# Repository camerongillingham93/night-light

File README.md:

# Firefly Night-Light
#### February, 13, 2025
 - Development REPO for a nightlight project using the AT-TINY1614 MCU and addressable LED strips
## Features 
 - PCB is designed to replace a standard wide-mouth Mason jar and have LED strips hanging from it resembling a jar full of fireflies
 - Top copper pad acts as a touch button to toggle the nightlight on/off and adjust brightness. Shake the jar for a firefly lightshow
 - Onboard LI-PO battery that is USB-C re-chargeable

<br>
*Rendering of Top of the night-light PCB*

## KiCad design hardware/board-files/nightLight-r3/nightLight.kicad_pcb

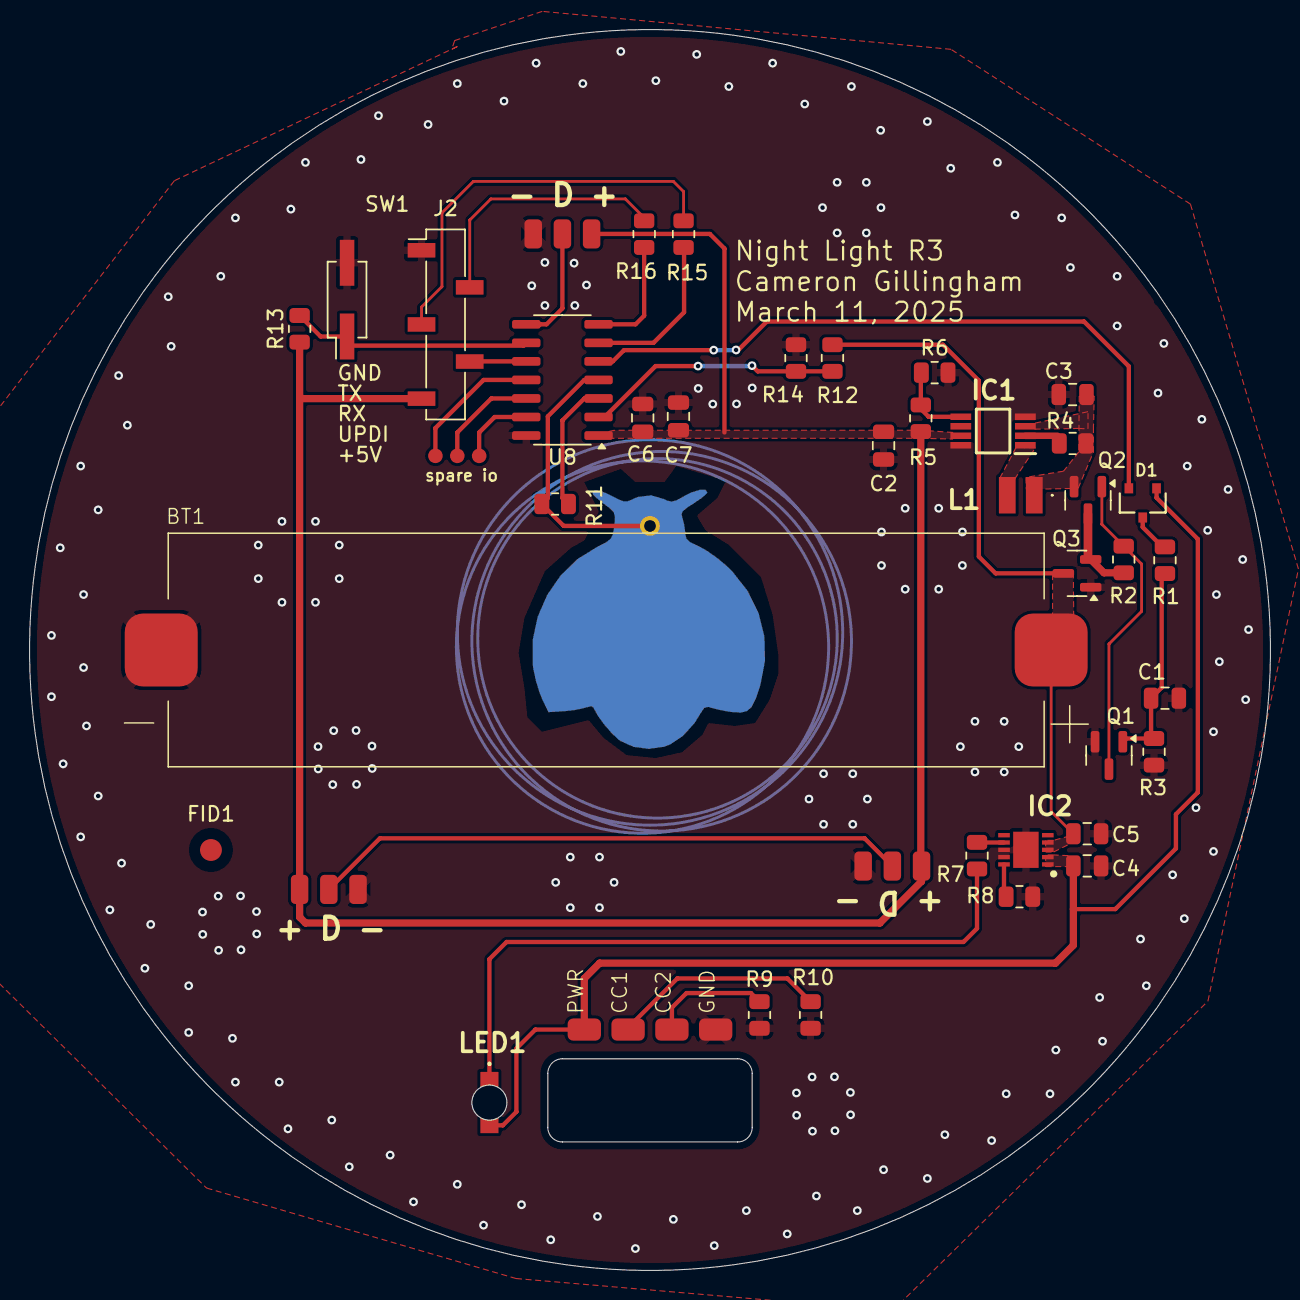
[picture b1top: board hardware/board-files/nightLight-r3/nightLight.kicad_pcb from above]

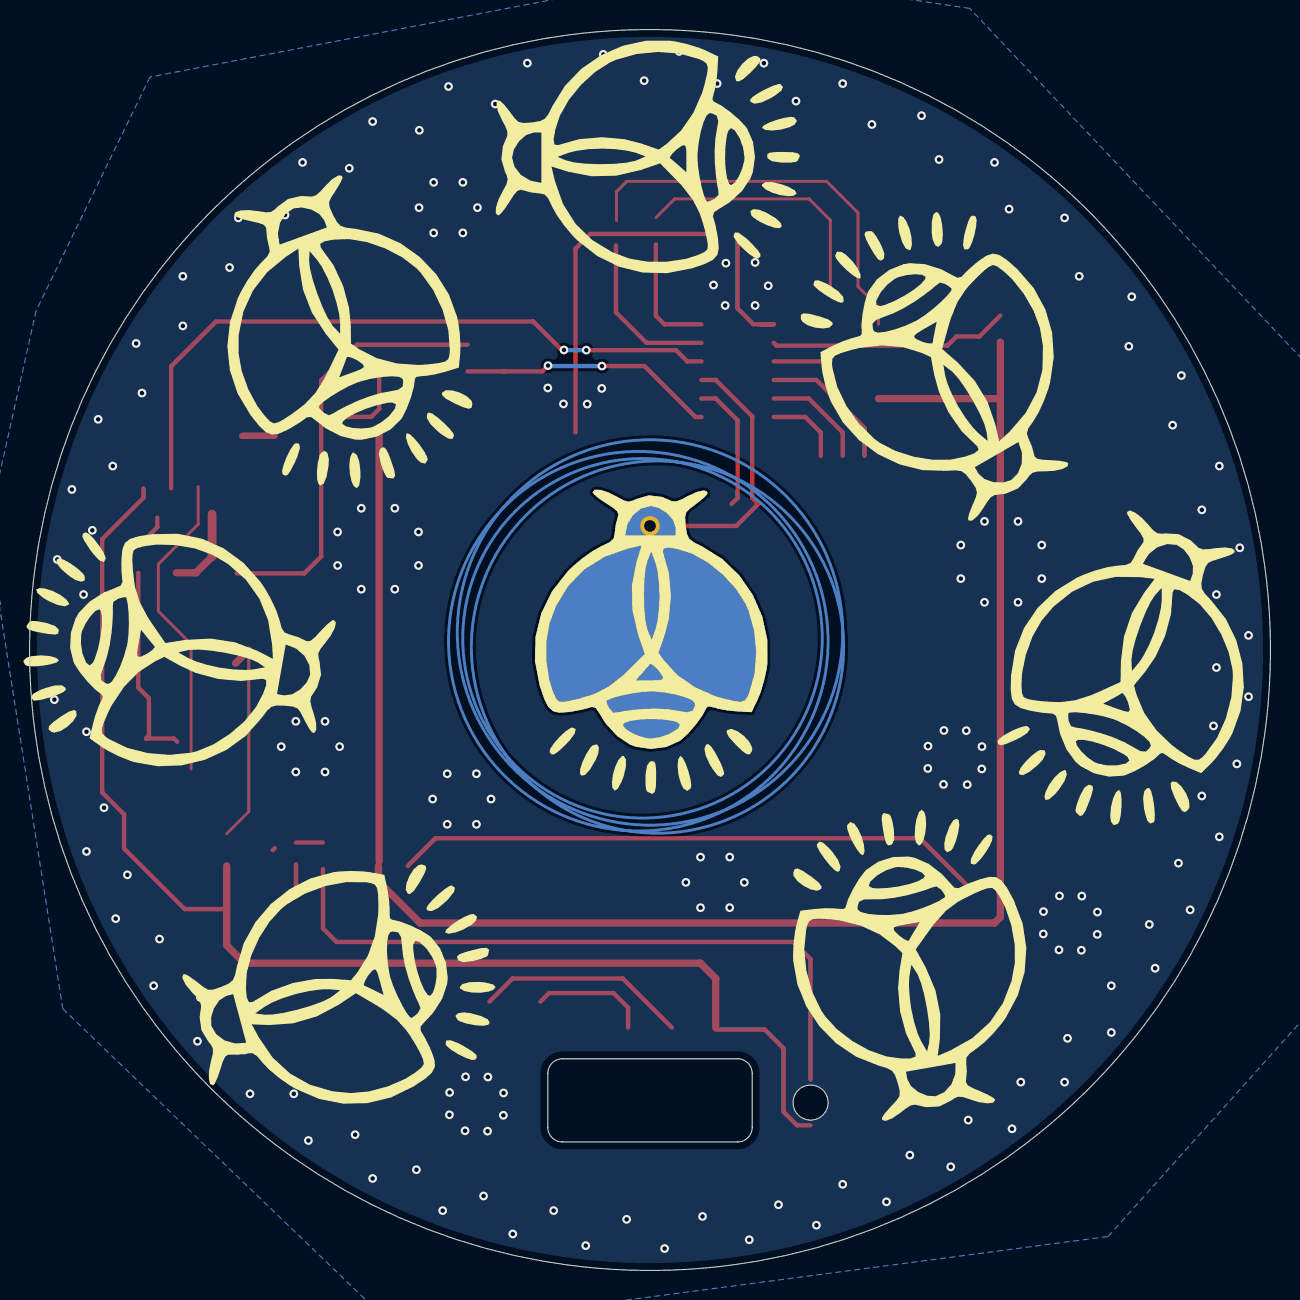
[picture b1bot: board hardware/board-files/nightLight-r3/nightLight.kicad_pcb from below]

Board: 2 copper layers, 85.0 x 85.0 mm, 49 parts (8 on the bottom side), 32 nets.

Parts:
B1: fireflyTouch
BT1: Battery_Cell; 14500 Holder
C1, C7: 0.1uF; C_0805_2012Metric
C2, C3, C6: 22uF; C_0805_2012Metric
C4, C5: 4.7uF; C_0805_2012Metric
D1: BAT54C; SOT23-R
FID1: Fiducial; Fiducial_1.5mm_Mask3mm
IC1: PAM2401SCADJ; SOP65P490X110-8N
IC2: MCP73123T-22SI_MF; SON50P300X300X100-11N-D
J1: USB_C_Receptacle_PowerOnly_6P; USB-C_PWR
J2: Conn_01x05_Pin; PinSocket_1x05_P2.54mm_Vertical_SMD_Pin1Left
J3: Conn_01x03; spares_1*3
J4, J5, J6: Conn_01x03; fairy_conn
L1: SRN2510BTA-2R2M; SRN2510BTA2R2M
LED1: IN-S124ARUW; INS124ARUW
Q1: AO3400A; SOT-23
Q2, Q3: AO3401A; SOT-23
R1: 10K; R_0805_2012Metric
R2, R3, R11, R12, R14: 1M; R_0805_2012Metric
R4, R5: 750K; R_0805_2012Metric
R6: 100K; R_0805_2012Metric
R7: 1K; R_0805_2012Metric
R8: 5.1K; R_0805_2012Metric
R9, R10: 5.1k; R_0805_2012Metric
R13: 10k; R_0805_2012Metric
R15, R16: 0; R_0805_2012Metric
SW1: TILT; PinHeader_2x01_P2.54mm_Vertical_SMD
U1, U2, U3, U4, U5, U6, U7: fireflyTouchNB
U8: ATtiny1614-SS; SOIC-14_3.9x8.7mm_P1.27mm

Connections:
+5V: C2.1, C6.1, C7.1, IC1.7 (OUT), J2.5, J4.1, J5.1, J6.1, R5.2, R13.1, U8.1 (VCC)
/Charge Controller/Vbatt: BT1.1 (+), C5.1, IC2.3 (VBAT_1), IC2.4 (VBAT_2), Q3.3 (D), R12.1
/Charge Controller/Vbus: C4.1, D1.1, IC2.1 (VDD_1), IC2.2 (VDD_2), J1.A9 (VBUS), LED1.2 (A)
/MCU/BATT_M: R12.2, R14.1, U8.2 (PA4)
/MCU/FET_CONTROL: D1.2, U8.5 (PA7)
/MCU/LED_DATA: J4.2, U8.8 (PB1)
/MCU/PA_1: J3.1, U8.11 (PA1)
/MCU/PA_2: J3.2, U8.12 (PA2)
/MCU/PA_3: J3.3, U8.13 (PA3)
/MCU/RETURN: B1.1, R11.2, U8.4 (PA6)
/MCU/RX: R15.1, U8.6 (PB3)
/MCU/SEND: R11.1, U8.3 (PA5)
/MCU/TILT_SW: R13.2, SW1.1, U8.9 (PB0)
/MCU/TX: R16.1, U8.7 (PB2)
/MCU/UPDI: J2.4, U8.10 (~RESET/PA0)
GND: BT1.2 (-), C1.2, C2.2, C3.2, C4.2, C5.2, C6.2, C7.2, IC1.4 (AGND), IC1.8 (PGND), IC2.8 (VSS_1), IC2.9 (VSS_2), IC2.11 (EP), J1.A12 (GND), J2.1, J4.3, J5.3, J6.3, Q1.2 (S), Q3.1 (G), R3.2, R6.1, R8.2, R9.2, R10.2, R14.2, SW1.2, U8.14 (GND)
unnamed: D1.3, R1.2
unnamed: IC1.2 (EN), R4.2
unnamed: IC1.5 (FB), R5.1, R6.2
unnamed: IC1.1 (LX), L1.2
unnamed: C3.1, IC1.3 (VIN), L1.1, Q2.2 (S), R4.1
unnamed: IC2.10 (PROG), R8.1
unnamed: IC2.7 (STAT), R7.2
unnamed: J1.A5 (CC1), R10.1
unnamed: J1.B5 (CC2), R9.1
unnamed: J2.2, R16.2
unnamed: J2.3, R15.2
unnamed: J5.2, J6.2
unnamed: LED1.1 (K), R7.1
unnamed: Q1.3 (D), Q2.1 (G), R2.2
unnamed: C1.1, Q1.1 (G), R1.1, R3.1
unnamed: Q2.3 (D), Q3.2 (S), R2.1

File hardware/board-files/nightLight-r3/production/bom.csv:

Designator,Footprint,Quantity,Value,LCSC Part #
B1,fireflyTouch,1,~,
BT1,14500 Holder,1,Battery_Cell,
"C1, C7",0805,2,0.1uF,
"C2, C3, C6",0805,3,22uF,
"C4, C5",0805,2,4.7uF,
D1,SOT23-R,1,BAT54C,
FID1,Fiducial_1.5mm_Mask3mm,1,Fiducial,
IC1,SOP65P490X110-8N,1,PAM2401SCADJ,
IC2,SON50P300X300X100-11N-D,1,MCP73123T-22SI_MF,
J1,USB-C_PWR,1,USB_C_Receptacle_PowerOnly_6P,
J2,PinSocket_1x05_P2.54mm_Vertical_SMD_Pin1Left,1,Conn_01x05_Pin,
J3,spares_1*3,1,Conn_01x03,
"J4, J5, J6",fairy_conn,3,Conn_01x03,
L1,SRN2510BTA2R2M,1,SRN2510BTA-2R2M,
LED1,INS124ARUW,1,IN-S124ARUW,
Q1,SOT-23,1,AO3400A,
"Q2, Q3",SOT-23,2,AO3401A,
"R1, R13",0805,2,10K,
"R10, R8, R9",0805,3,5.1k,
"R11, R12, R14, R2, R3",0805,5,1M,
"R15, R16",0805,2,0,
"R4, R5",0805,2,750K,
R6,0805,1,100K,
R7,0805,1,1K,
SW1,PinHeader_2x01_P2.54mm_Vertical_SMD,1,TILT,
U8,SOIC-14_3.9x8.7mm_P1.27mm,1,ATtiny1614-SS,

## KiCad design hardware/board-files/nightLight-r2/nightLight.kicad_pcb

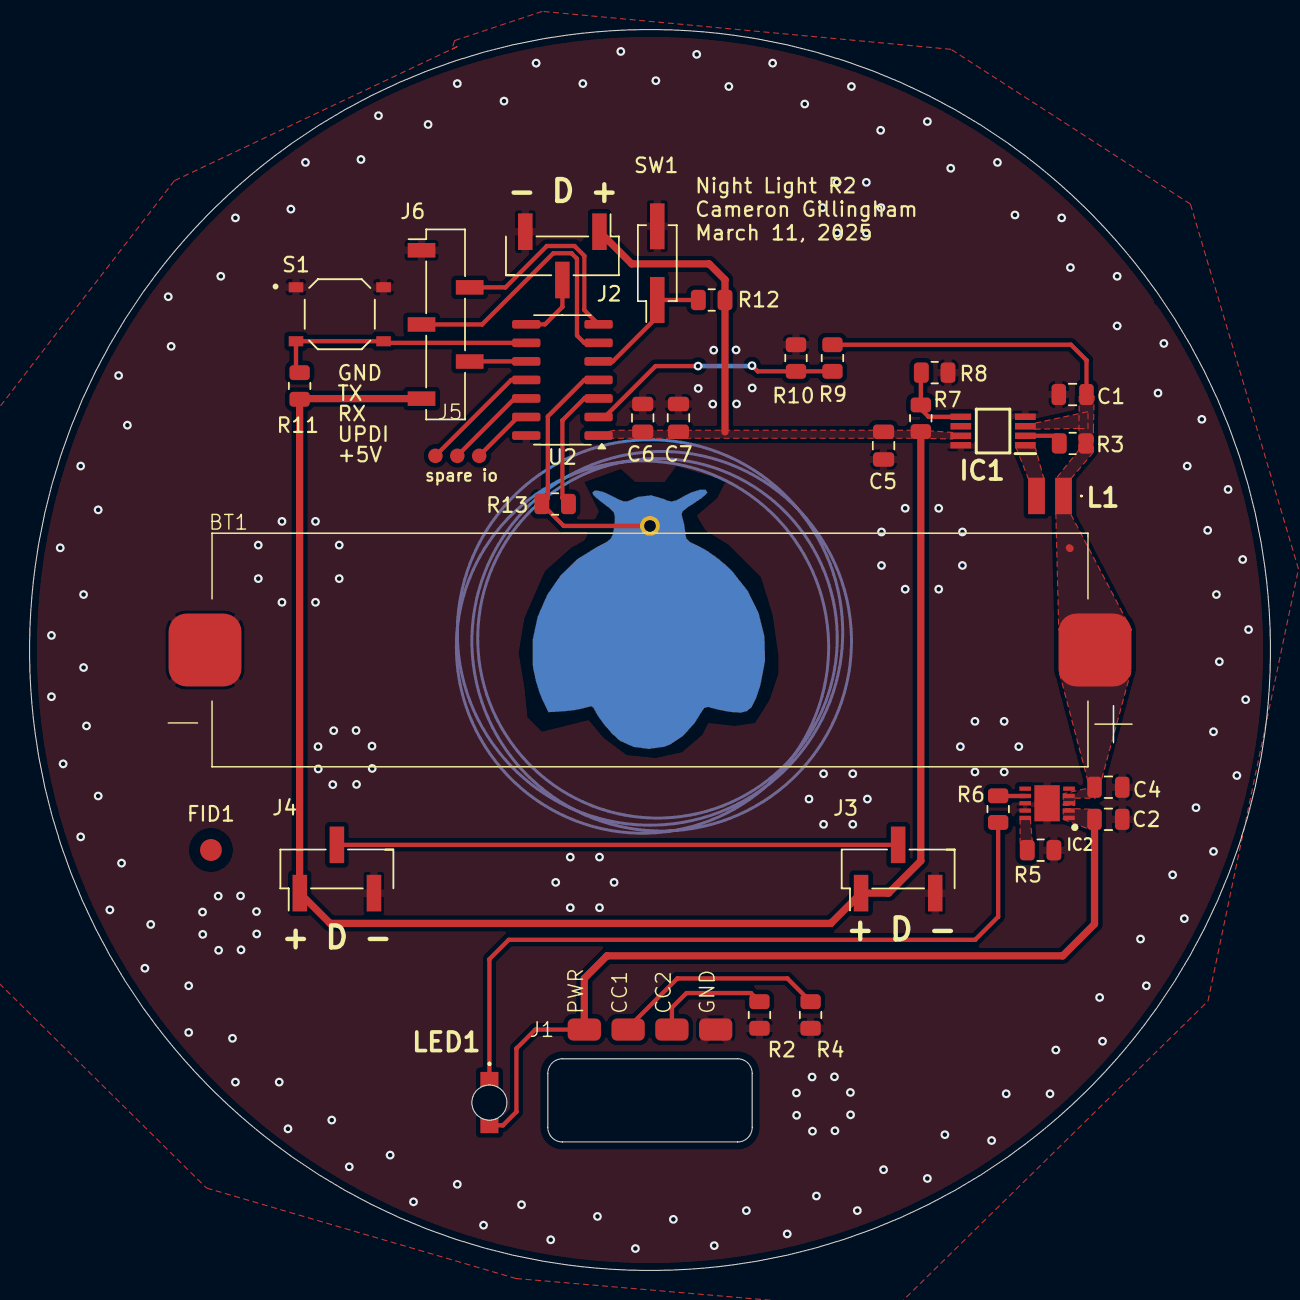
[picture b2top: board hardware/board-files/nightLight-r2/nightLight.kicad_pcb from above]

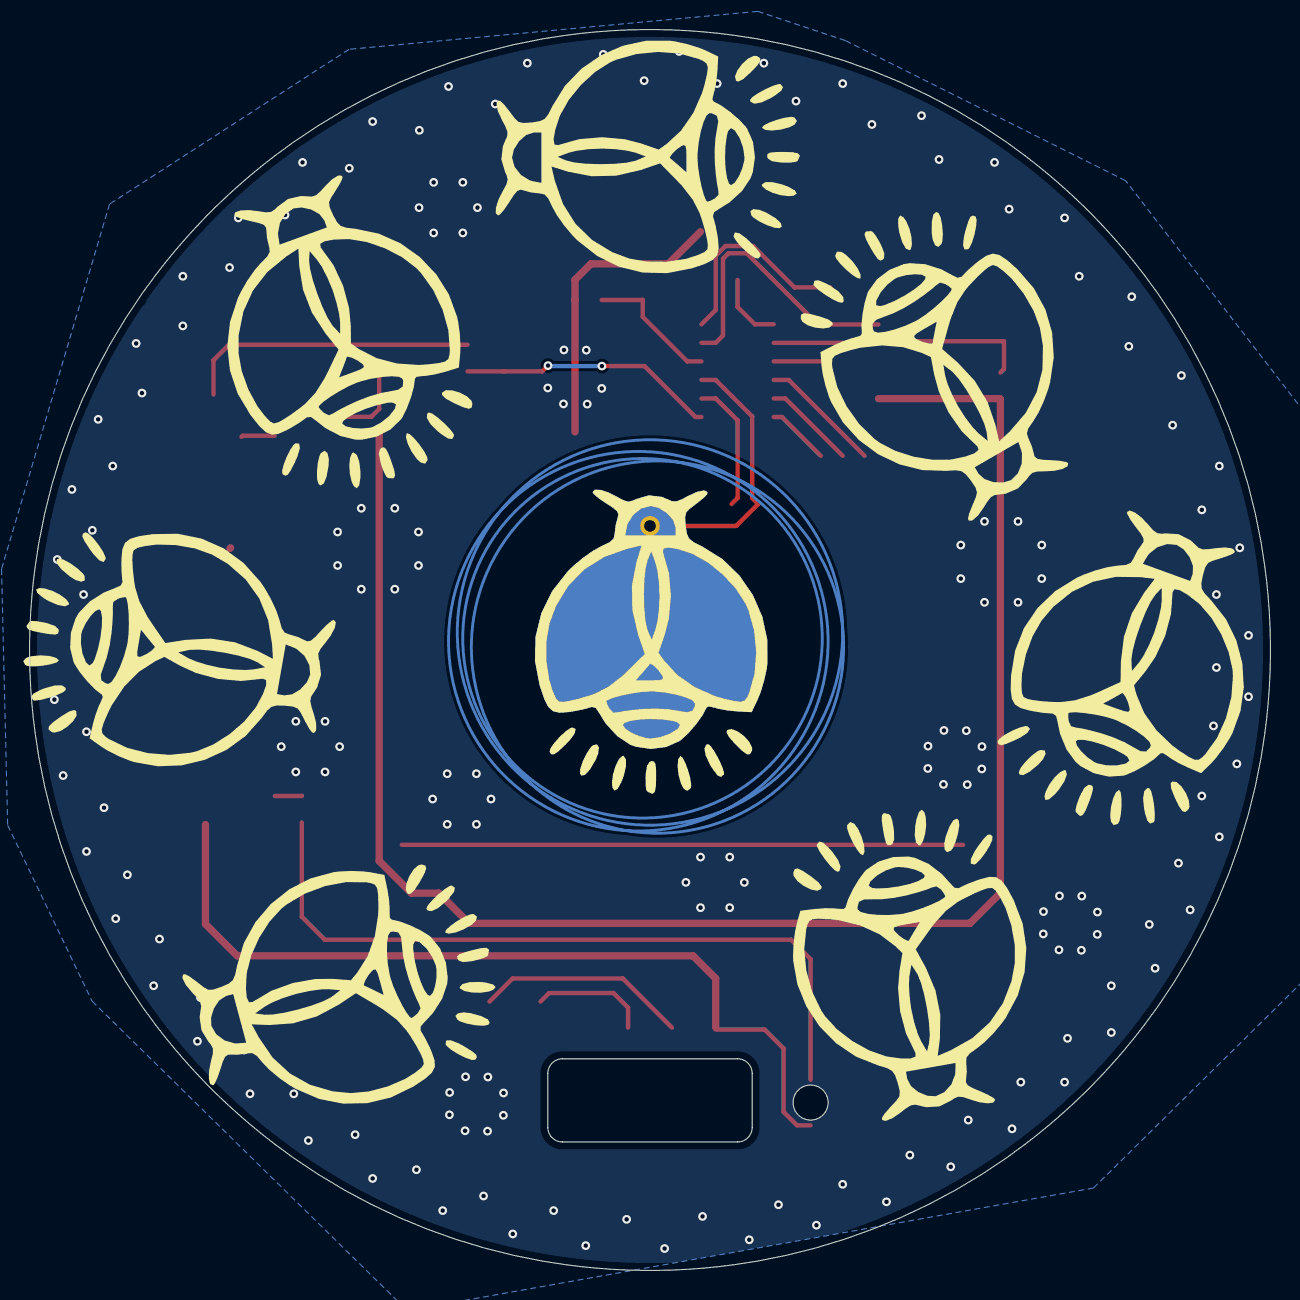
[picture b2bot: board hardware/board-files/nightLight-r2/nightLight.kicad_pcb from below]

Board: 2 copper layers, 85.0 x 85.0 mm, 41 parts (8 on the bottom side), 25 nets.

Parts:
B1: fireflyTouch
BT1: Battery_Cell; 14500 Holder
C1, C5, C6: 22uF; C_0805_2012Metric
C2, C4: 4.7uF; C_0805_2012Metric
C7: 0.1uF; C_0805_2012Metric
FID1: Fiducial; Fiducial_1.5mm_Mask3mm
IC1: PAM2401SCADJ; SOP65P490X110-8N
IC2: MCP73123T-22SI_MF; SON50P300X300X100-11N-D
J1: USB_C_Receptacle_PowerOnly_6P; USB-C_PWR
J2, J3, J4: Conn_01x03; PinHeader_1x03_P2.54mm_Vertical_SMD_Pin1Left
J5: Conn_01x03; spares_1*3
J6: Conn_01x05_Pin; PinSocket_1x05_P2.54mm_Vertical_SMD_Pin1Left
L1: SRN2510BTA-2R2M; SRN2510BTA2R2M
LED1: IN-S124ARUW; INS124ARUW
R2, R4: 5.1k; R_0805_2012Metric
R3, R7: 750K; R_0805_2012Metric
R5: 5.1K; R_0805_2012Metric
R6: 1K; R_0805_2012Metric
R8: 100K; R_0805_2012Metric
R9, R10: 0; R_0805_2012Metric
R11, R12: 10k; R_0805_2012Metric
R13: 1M; R_0805_2012Metric
S1: PTS526_SM08_SMTR2_LFS; SW_PTS526_SM08_SMTR2_LFS
SW1: TILT; PinHeader_2x01_P2.54mm_Vertical_SMD
U2: ATtiny1614-SS; SOIC-14_3.9x8.7mm_P1.27mm
U3, U4, U5, U6, U7, U8, U9: fireflyTouchNB

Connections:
+5V: C5.1, C6.1, C7.1, IC1.7 (OUT), J2.1, J3.1, J4.1, J6.5, R7.2, R11.1, R12.1, U2.1 (VCC)
Batt_M: R9.2, R10.1, U2.2 (PA4)
GND: BT1.2 (-), C1.2, C2.2, C4.2, C5.2, C6.2, C7.2, IC1.4 (AGND), IC1.8 (PGND), IC2.8 (VSS_1), IC2.9 (VSS_2), IC2.11 (EP), J1.A12 (GND), J2.3, J3.3, J4.3, J6.1, R2.2, R4.2, R5.2, R8.1, R10.2, S1.1, S1.2, SW1.2, U2.14 (GND)
LED_DATA: J2.2, U2.8 (PB1)
unnamed: IC1.2 (EN), R3.2
unnamed: IC1.5 (FB), R7.1, R8.2
unnamed: IC1.1 (LX), L1.2
unnamed: IC2.10 (PROG), R5.1
unnamed: IC2.7 (STAT), R6.2
unnamed: C2.1, IC2.1 (VDD_1), IC2.2 (VDD_2), J1.A9 (VBUS), LED1.2 (A)
unnamed: J1.A5 (CC1), R4.1
unnamed: J1.B5 (CC2), R2.1
unnamed: J3.2, J4.2
unnamed: LED1.1 (K), R6.1
PA_1: J5.1, U2.11 (PA1)
PA_2: J5.2, U2.12 (PA2)
PA_3: J5.3, U2.13 (PA3)
RST_SW: R11.2, S1.3, S1.4, U2.9 (PB0)
RX: J6.3, U2.6 (PB3)
Return: B1.1, R13.2, U2.4 (PA6)
Send: R13.1, U2.3 (PA5)
TX: J6.2, U2.7 (PB2)
Tilt_SW: R12.2, SW1.1, U2.5 (PA7)
UPDI: J6.4, U2.10 (~RESET/PA0)
VBATT: BT1.1 (+), C1.1, C4.1, IC1.3 (VIN), IC2.3 (VBAT_1), IC2.4 (VBAT_2), L1.1, R3.1, R9.1

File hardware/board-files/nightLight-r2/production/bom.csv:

Designator,Footprint,Quantity,Value,LCSC Part #,,Mouser Cart,Already Have,JLC,Wal-Mart Batteries,,
B1,fireflyTouch,1,~,,,N/A,X,,https://www.walmart.ca/en/ip/12-Pack-AA-3-2-Volt-600-mAh-LiF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,,
BT1,14500 Holder,1,Battery_Cell,,,N/A,X,,,,
"C1, C5, C6",0805,3,22uF,,,X,,,,,
"C2, C4",0805,2,4.7uF,,,X,,,,,
C7,0805,1,0.1uF,,,X,,,,,
FID1,Fiducial_1.5mm_Mask3mm,1,Fiducial,,,,X,,,,
IC1,SOP65P490X110-8N,1,PAM2401SCADJ,,,X,,,,,
IC2,SON50P300X300X100-11N-D,1,MCP73123T-22SI_MF,,,X,,,,,
J1,USB-C_PWR,1,USB_C_Receptacle_PowerOnly_6P,,,,X,,,,
"J2, J3, J4",PinHeader_1x03_P2.54mm_Vertical_SMD_Pin1Left,3,Conn_01x03,,,,X,,,,
J5,spares_1*3,1,Conn_01x03,,,,X,,,,
J6,PinSocket_1x05_P2.54mm_Vertical_SMD_Pin1Left,1,Conn_01x05_Pin,,,,X,,,,
L1,SRN2510BTA2R2M,1,SRN2510BTA-2R2M,,,X,,,,,
LED1,INS124ARUW,1,IN-S124ARUW,,,X,,,,,
"R10, R9",0805,2,0,,,X,,,,,
"R11, R12",0805,2,10k,,,X,,,,,
R13,0805,1,1M,,,X,,,,,
"R2, R4, R5",0805,3,5.1k,,,X,,,,,
"R3, R8",0805,2,100K,,,X,,,,,
R6,0805,1,1K,,,X,,,,,
R7,0805,1,750K,,,X,,,,,
S1,SW_PTS526_SM08_SMTR2_LFS,1,PTS526_SM08_SMTR2_LFS,,,X,,,,,
SW1,PinHeader_2x01_P2.54mm_Vertical_SMD,1,TILT,,,,X,,,,
U1,SOT95P237X112-3N,1,MCP809T-270I_TT,,,X,,,,,
U2,SOIC-14_3.9x8.7mm_P1.27mm,1,ATtiny1614-SS,,,X,,,,,
,,,,,,,,,,,
Total,,,,,,80,0,19.16,85.77,,184.93
/unit,,,,,,8,,3.83,7,,18.83

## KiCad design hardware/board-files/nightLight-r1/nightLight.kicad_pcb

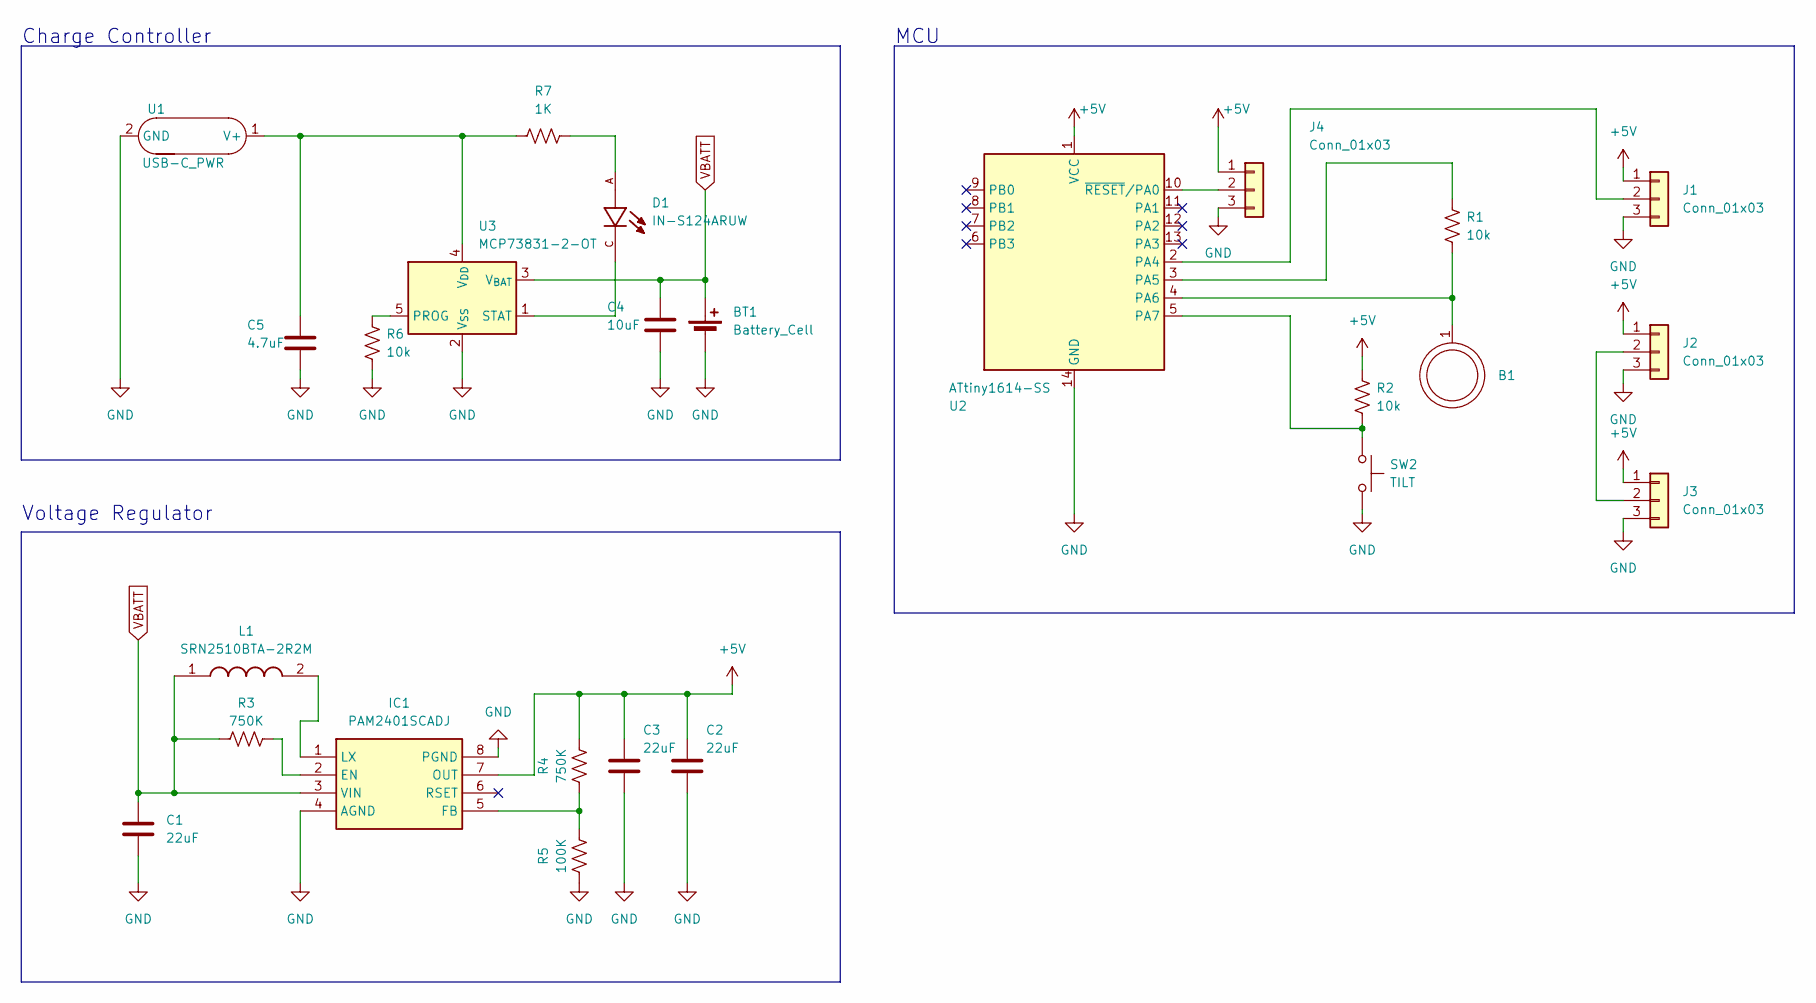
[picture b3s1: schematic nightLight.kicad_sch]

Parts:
B1: fireflyTouch
BT1: Battery_Cell; 14500 Holder
C1, C2, C3: 22uF; C_1206_3216Metric
C4: 10uF; C_1206_3216Metric
C5: 4.7uF; C_1206_3216Metric
D1: IN-S124ARUW; LED_IN-S124ARUW
IC1: PAM2401SCADJ; SOP65P490X110-8N; Mouser Part Number 621-PAM2401SCADJ
J1, J2, J3, J4: Conn_01x03; PinHeader_1x03_P2.54mm_Vertical_SMD_Pin1Left
L1: SRN2510BTA-2R2M; SRN2510BTA2R2M; Mouser Part Number 652-SRN2510BTA-2R2M
R1, R2, R6: 10k; R_1206_3216Metric
R3, R4: 750K; R_1206_3216Metric
R5: 100K; R_1206_3216Metric
R7: 1K; R_1206_3216Metric
SW2: TILT; PinHeader_2x01_P2.54mm_Vertical_SMD
U1: USB-C_PWR
U2: ATtiny1614-SS; SOIC-14_3.9x8.7mm_P1.27mm
U3: MCP73831-2-OT; SOT-23-5

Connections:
+5V: C2.1, C3.1, IC1.7 (OUT), J1.1, J2.1, J3.1, J4.1, R2.1, R4.2, U2.1 (VCC)
GND: BT1.2 (-), C1.2, C2.2, C3.2, C4.2, C5.2, IC1.4 (AGND), IC1.8 (PGND), J1.3, J2.3, J3.3, J4.3, R5.1, R6.2, SW2.2, U1.2 (GND), U2.14 (GND), U3.2 (V_{SS})
unnamed: D1.A, R7.2
unnamed: IC1.2 (EN), R3.2
unnamed: IC1.5 (FB), R4.1, R5.2
unnamed: IC1.1 (LX), L1.2
unnamed: J1.2, U2.2 (PA4)
unnamed: J2.2, J3.2
unnamed: J4.2, U2.10 (~RESET/PA0)
unnamed: C5.1, R7.1, U1.1 (V+), U3.4 (V_{DD})
unnamed: R1.1, U2.3 (PA5)
unnamed: B1.1, R1.2, U2.4 (PA6)
unnamed: R2.2, SW2.1, U2.5 (PA7)
unnamed: R6.1, U3.5 (PROG)
unnamed: D1.C, U3.1 (STAT)
VBATT: BT1.1 (+), C1.1, C4.1, IC1.3 (VIN), L1.1, R3.1, U3.3 (V_{BAT})

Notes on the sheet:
Voltage Regulator
MCU
Charge Controller

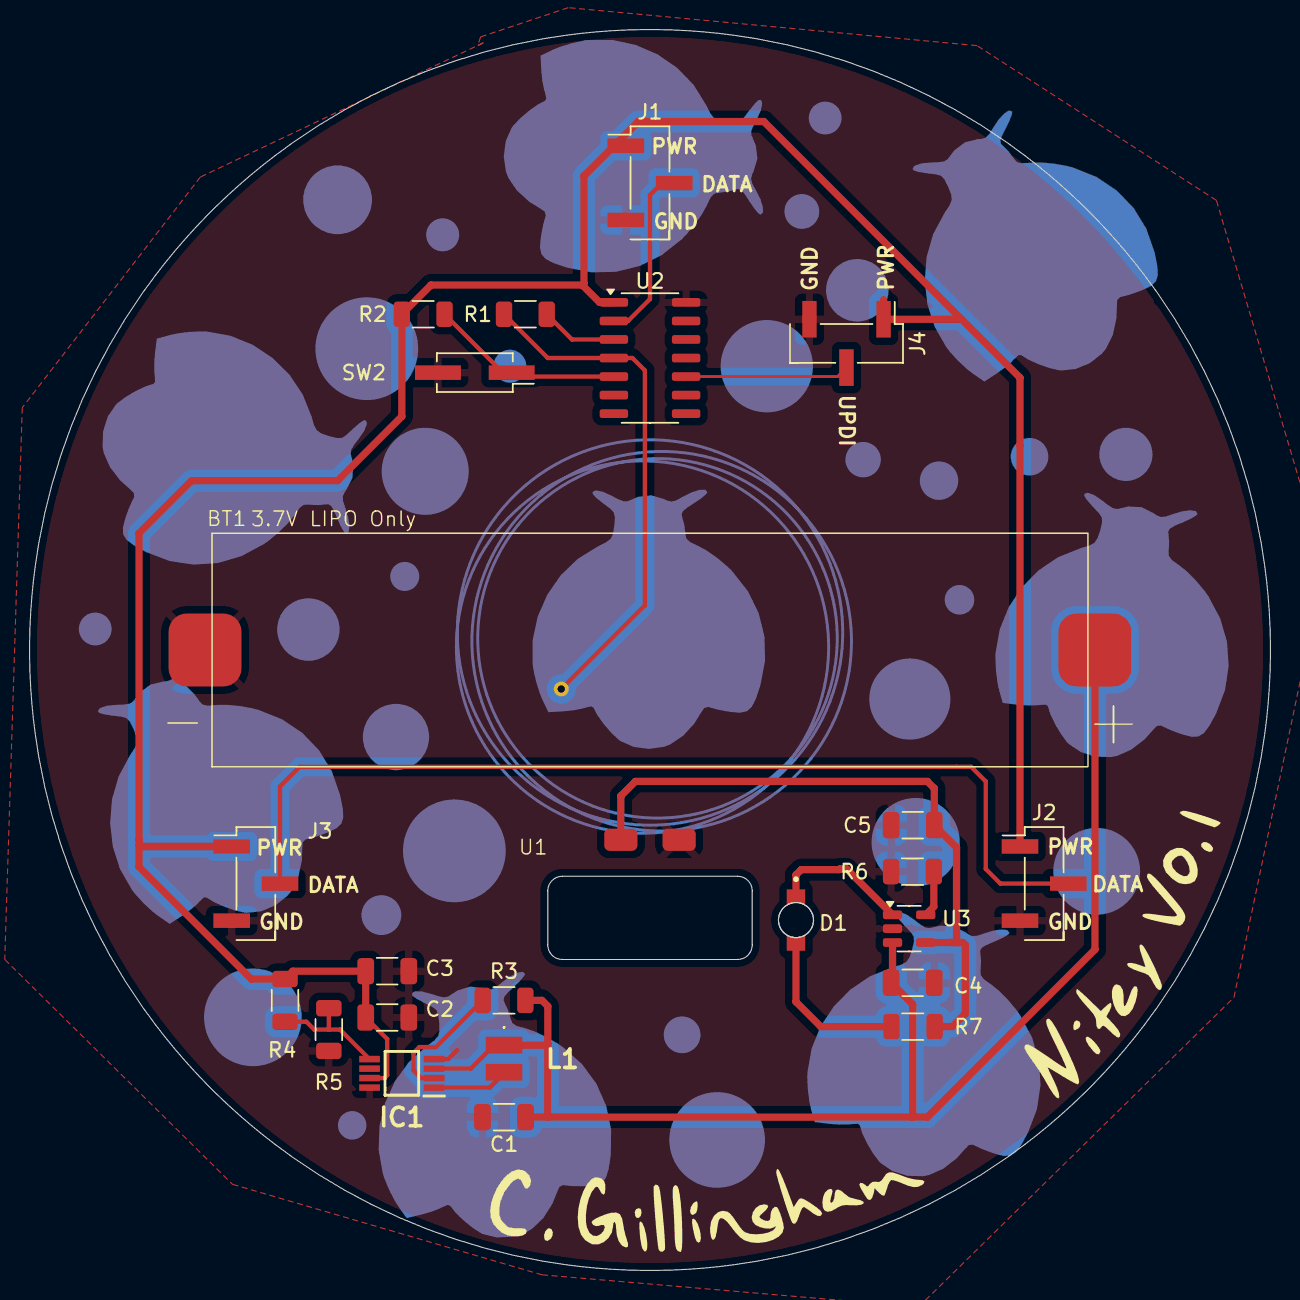
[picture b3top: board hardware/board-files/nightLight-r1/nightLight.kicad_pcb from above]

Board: 2 copper layers, 85.0 x 85.0 mm, 25 parts (1 on the bottom side), 16 nets.

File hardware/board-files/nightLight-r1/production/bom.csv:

Designator,Footprint,Quantity,Value,LCSC Part #
B1,fireflyTouch,1,~,
BT1,14500 Holder,1,Battery_Cell,
"C1, C2, C3",1206,3,22uF,
C4,1206,1,10uF,
C5,1206,1,4.7uF,
D1,LED_IN-S124ARUW,1,IN-S124ARUW,
IC1,SOP65P490X110-8N,1,PAM2401SCADJ,
"J1, J2, J3, J4",PinHeader_1x03_P2.54mm_Vertical_SMD_Pin1Left,4,Conn_01x03,
L1,SRN2510BTA2R2M,1,SRN2510BTA-2R2M,
"R1, R2, R6",1206,3,10k,
"R3, R4",1206,2,750K,
R5,1206,1,100K,
R7,1206,1,1K,
SW2,PinHeader_2x01_P2.54mm_Vertical_SMD,1,TILT,
U1,USB-C_PWR,1,USB-C_PWR,
U2,SOIC-14_3.9x8.7mm_P1.27mm,1,ATtiny1614-SS,
U3,SOT-23-5,1,MCP73831-2-OT,

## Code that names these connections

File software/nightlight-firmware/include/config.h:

#ifndef CONFIG_H
#define CONFIG_H

// Pin definitions and constants

// Touch Sensor Pins and Threshold
#define sensePin PIN_PA5
#define refPin PIN_PA6
#define tiltSW PIN_PB0
#define touchThreshold 5

#define battMeasure PIN_PA4

// NeoPixel LED Strip Setup
#define LED_PIN PIN_PB1
#define NUM_PIXELS 10

// Brightness control
#define BRIGHTNESS_STEP 7
#define MIN_BRIGHTNESS 30
#define MAX_BRIGHTNESS 255

// Power management settings
#define POWER_CONTROL_PIN PIN_PA7
#define SLEEP_TIMEOUT_MS                                                       \
  30000 // 180000        // 3 minutes of inactivity before sleep
#define CRITICAL_BATTERY_THRESHOLD 2.8 // Volts - hard shutdown
#define WAKEUP_BATTERY_THRESHOLD 2.9   // Volts - can wake up again (hysteresis)
#define WAKEUP_TILT_DURATION 3000     // 3 seconds upside down to wake up

#endif

// **IMPORTANT: Double-check these pin numbers against your ATtiny1614 board's
// pinout!**
// sensePin: PA5
// refPin:   PA6
// tiltSW:   PB0
// battMeasure: PA4
// LED_PIN:  PB1
// POWER_CONTROL_PIN: PA7

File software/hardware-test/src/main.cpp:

#include <Arduino.h>
// /*
// February 7 2025

// Sketch to test the hardware components of the nightLight PCB.

// Uses a modded USB-UART device to flash the AT-tiny 1614, Select Serial UPDI
// -SLOW as prgogrammer

// Pins must be labelled as "PIN_PA2"
// */

// #include <tinyNeoPixel.h>

// #define LED_DATA_PIN PIN_PA4 // Data pin for RGB strand
// #define CONTROL_PIN PIN_PA6
// #define SENSE_PIN PIN_PA5

// #define NUMPIXELS 15

// tinyNeoPixel pixels =
//     tinyNeoPixel(NUMPIXELS, LED_DATA_PIN, NEO_GRB + NEO_KHZ800);

// int sensorThreshold = 700;
// bool toggle = 0;
// bool lastState = 0;

// uint16_t senseTouch();

// void setup() {
//   pixels.begin(); // This initializes the NeoPixel library.
//   Serial.begin(4800);
// }

// void loop() {
//   Serial.println("Hello CAM");
//   uint16_t sensorValue = senseTouch();
//   Serial.println(sensorValue);

//   bool currentState = (sensorValue < sensorThreshold);

//   if (currentState && !lastState) {
//     toggle = !toggle;
//     if (toggle) {
//       pixels.setPixelColor(
//           1, pixels.Color(0, 150, 0)); // Moderately bright green color.
//     } else {
//       pixels.clear();
//     }
//     pixels.show();
//   }

//   lastState = currentState;
// }

// uint16_t senseTouch() {
//   pinMode(CONTROL_PIN, OUTPUT);
//   digitalWrite(CONTROL_PIN, LOW); // Discharge through CONTROL_PIN

//   pinMode(SENSE_PIN, INPUT);
//   uint16_t count = 0;

//   // Charge the pad through the 1MΩ resistor
//   pinMode(CONTROL_PIN, INPUT); // Let it float
//   while (digitalRead(SENSE_PIN) == LOW) {
//     count++;
//     if (count > 1000)
//       break; // Prevent infinite loop
//   }

//   return count; // Higher count = more capacitance (finger detected)
// }
#define pinBatteryVoltage PIN_PA4 // ADC input pin (connected to divider midpoint)

void setup() {
  Serial.begin(9600);
  while (!Serial)
    ; // Wait for Serial if necessary
}

void loop() {
  uint16_t rawADC = analogRead(pinBatteryVoltage);

  // ADC reference = 5V (regulated VDD)
  // Battery is divided in half, so multiply by 2 to recover real voltage
  float batteryVoltage = (rawADC / 1023.0) * 5.0 * 2.0;

  Serial.print("Battery Voltage: ");
  Serial.print(batteryVoltage, 2);
  Serial.println(" V");

  delay(1000); // Read once per second
}

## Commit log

2025-02-13 init
    created hardware and software folder and placed up to date dev files in them
2025-02-13 added current hardware-test file
2025-02-13 renames
2025-02-13 Added hardware r1 notes
2025-02-13 made readme
2025-02-13 caption
2025-02-13 edit
2025-02-13 added gitignore
2025-02-13 Remove .DS_Store from tracking
2025-02-13 Added datasheets
2025-02-13 gitignore
2025-02-13 removed files
2025-02-14 todo list
2025-02-14 made notes and created pin map
2025-02-14 created new folder for PCB R2
2025-02-15 pin map
2025-02-20 Finished schematic, started PCB. Figuring out copper zones
2025-02-21 first PCB layout done
2025-02-21 Finished first PCB revision
2025-02-21 Created project for firmware r1 and included some files to test PTC
2025-02-21 updated TODO list
2025-02-25 refactored entirely, had it working and then broke again
2025-02-25 Updated notes
2025-02-25 Fixed Serial monitor, had clk speed set to 2Mhz instead of 20Mhz
2025-02-25 main-flow
2025-02-25 blocks added
2025-03-08 saved?
2025-03-11 updated TODO
2025-03-11 Finished PCB
2025-03-11 Touch sensor works to toggle LEDS reliably
2025-03-11 long press adjusting brightness works, some sort of weird grounding issue though
2025-03-14 Finished new design, needs to be reviewed and rid of errors
2025-03-15 generated fab files
2025-03-15 inventory
2025-03-17 shaker works, need it to implement it now
2025-03-21 hella buggy
2025-04-13 messing around during testing
2025-04-13 added notes
2025-04-13 hello
2025-04-13 not compliling
2025-04-14 Most features working well, Shake effect just needs to be added in.
2025-04-15 Firmware V1 complete
2025-04-15 trying to fix PCB files
2025-04-15 restored PCB files
2025-04-15 i commit
2025-04-15 added note
2025-04-15 removed print statements
2025-04-15 Added headers and removed unnused code
2025-04-15 Made folder for next PCB revision
2025-04-15 remove unnecessry code
2025-04-15 cleaned .ini file
2025-04-15 Check battery once a minute, and also add upper and lower threshold for entering/exiting LOW BATT mode
2025-04-15 less LEDS's, lower brightness max
2025-04-15 Tinker with threshold values
2025-04-17 kicad was opened
2025-04-17 added falstad cct
2025-04-17 new notes
2025-04-18 Added filter to latching cct
2025-04-21 Added LCD cct and broke schematics into different sheets
2025-04-22 finished shematic and added to PCB
2025-04-22 first layout revision
2025-04-22 notes
2025-04-22 PCB rev 3.1 done
2025-04-23 seems to be mostly working, but havent tested extensively
    - need to check battery voltage on a timer while asleep
2025-04-23 power control goes low, but does not return high
2025-04-23 needs work
2025-04-23 rev3 done, errors eliminated
2025-05-21 PCB R3 Finished and ordered
2025-05-29 used cont
2025-05-29 Fixed Bugs, added wakeEffect, adjust sleep timeout time
2025-05-30 fixed bugs, added wake up effect, extended sleep timeout
2025-07-06 working on BOM
2025-07-14 updated pins
2025-07-14 reveuwiung board
2025-07-14 removed low batt warning
2025-07-14 added defines
2025-07-20 things are not working, maybe revert to last commit?
2025-07-24 drew outline for bodge
2025-07-24 Fixed tilt2wake feature, ISR was looking at the port for the old pin i was using... need to add sleep check now that thats working
2025-08-10 in prog
